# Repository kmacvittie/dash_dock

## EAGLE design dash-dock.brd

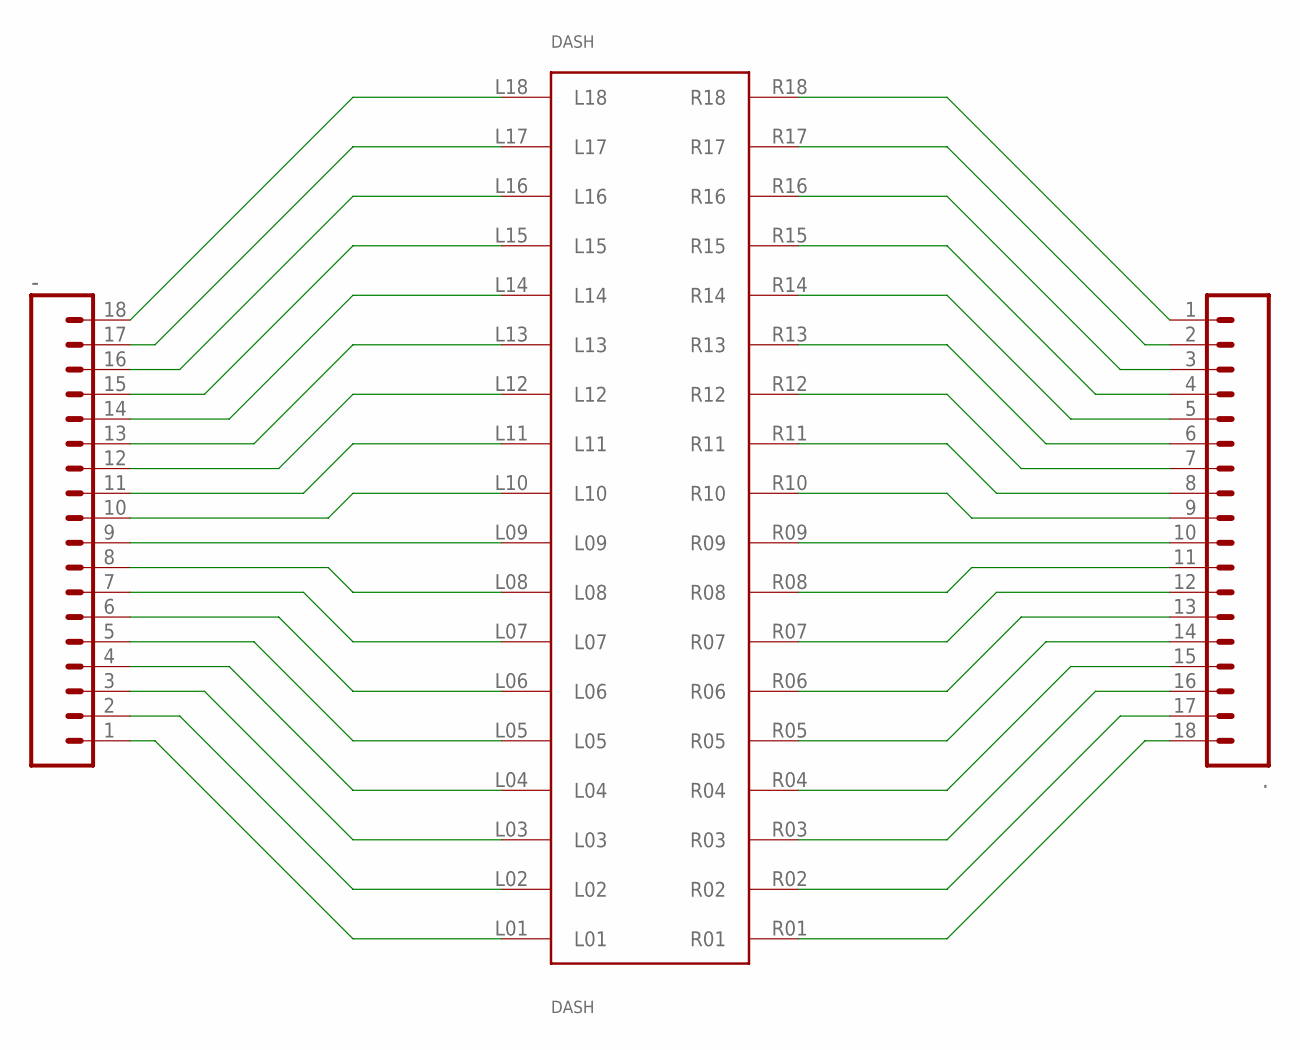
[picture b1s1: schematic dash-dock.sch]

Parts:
-: CONN_18; 1X18
.: CONN_18; 1X18
DASH: DASH

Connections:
GND: -.2, ..17, DASH.L02, DASH.R02
unnamed: -.9, DASH.L09
unnamed: -.10, DASH.L10
unnamed: -.11, DASH.L11
unnamed: -.12, DASH.L12
unnamed: -.13, DASH.L13
unnamed: -.14, DASH.L14
unnamed: -.15, DASH.L15
unnamed: -.16, DASH.L16
unnamed: -.17, DASH.L17
unnamed: -.18, DASH.L18
unnamed: -.8, DASH.L08
unnamed: -.7, DASH.L07
unnamed: -.6, DASH.L06
unnamed: -.5, DASH.L05
unnamed: -.4, DASH.L04
unnamed: -.3, DASH.L03
unnamed: -.1, DASH.L01
unnamed: ..10, DASH.R09
unnamed: ..9, DASH.R10
unnamed: ..8, DASH.R11
unnamed: ..7, DASH.R12
unnamed: ..6, DASH.R13
unnamed: ..5, DASH.R14
unnamed: ..4, DASH.R15
unnamed: ..3, DASH.R16
unnamed: ..2, DASH.R17
unnamed: ..1, DASH.R18
unnamed: ..11, DASH.R08
unnamed: ..12, DASH.R07
unnamed: ..13, DASH.R06
unnamed: ..14, DASH.R05
unnamed: ..15, DASH.R04
unnamed: ..16, DASH.R03
unnamed: ..18, DASH.R01

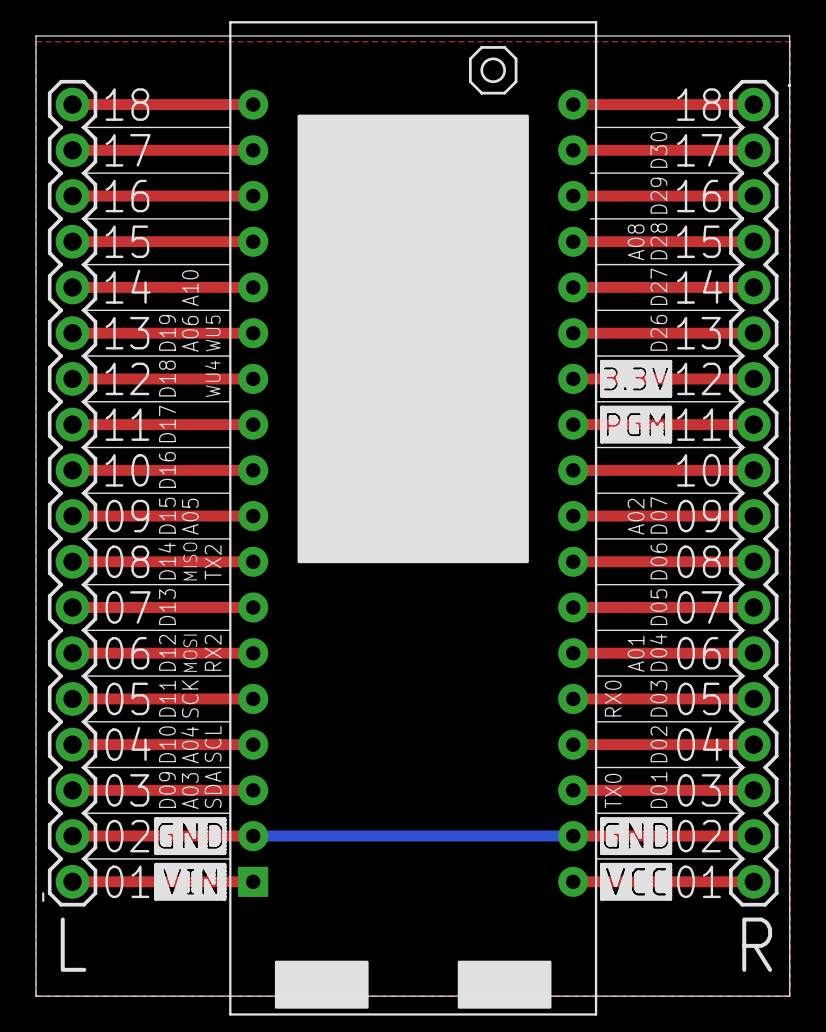
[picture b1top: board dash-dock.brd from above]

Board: 2 copper layers, 41.9 x 53.3 mm, 3 parts (0 on the bottom side), 35 nets.

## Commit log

2018-02-20 version 0.1
2018-03-03 updated gitignore

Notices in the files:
parts and their libraries:
SparkFun-Connectors: Licensing: Creative Commons ShareAlike 4.0 International - https://creativecommons.org/licenses/by-sa/4.0
